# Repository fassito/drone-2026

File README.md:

# Drone-2026

Controladora de vuelo para cuadricóptero basada en **ESP32 (DevKit V1)**,
programada con el **framework Arduino** bajo **PlatformIO**.

## Objetivos del proyecto

1. **Controladora de vuelo en ESP32** con bucle de estabilización a 1 kHz:
   PID en cascada (lazo externo de ángulo + lazo interno de velocidad angular).
2. **Accionamiento de 4 motores brushless** mediante ESC programables
   **BLHeli 30A** con protocolo **OneShot125** (3–6S LiPo).
3. **Doble enlace de comunicación**:
   - **RF** con emisora **FlySky FS-i6** + receptor **FS-IA6B** (protocolo iBus por UART).
   - **WiFi** con interfaz de línea de comandos (CLI) para diagnóstico,
     pruebas y telemetría en tiempo real.
4. **Autoajuste de parámetros PID** para la estabilización.
5. **Seguridad como requisito de primer orden**: armado explícito,
   failsafe de radio y WiFi, corte de motores y procedimientos de prueba seguros.

## Lista de materiales (BOM)

| Componente | Referencia | Notas |
|---|---|---|
| Microcontrolador | ESP32 DevKit V1 (ESP32-WROOM-32, 30 pines) | 240 MHz, dual-core, WiFi |
| Motores | 4× Crozepony DX2205 | 2300 KV, brushless |
| ESC | 4× BLHeli 30A | OneShot125, 3–6S |
| PDB | Power Distribution Board con XT-60 | Reparte la batería a los 4 ESC y al BEC |
| Receptor | FlySky FS-IA6B | 6 canales, iBus UART 115200 |
| Emisora | FlySky FS-i6 | 6 canales, AFHDS 2A, compatible con iBus |
| Batería | LiPo **4S 1550 mAh** (14.8 V) | Alimenta ESCs; BEC/regulador para el ESP32 |
| IMU | MPU-9250 (GY-951) | 9DoF por SPI; fusión Madgwick en el ESP32 a 1 kHz |
| GPS | u-blox NEO-6M-0-001 | NMEA por UART 9600; navegación, waypoints y RTH |
| Monitor de batería | INA219 (I2C) | Monitor de tensión y corriente; alimenta el failsafe de batería baja |
| Barómetro | BMP388 (I2C) | Altitud barométrica para mantener altura con precisión |
| Telemetría en vuelo | HC-12 (433/868/915 MHz) | Enlace bidireccional de comandos/telemetría, fuera de la banda 2.4 GHz |
| Pantalla | OLED I2C ~1" (SSD1306/SH1106) | Telemetría y diagnóstico en pantalla |
| Proximidad | 4× Sharp GP2Y0A21 (IR analógico) | Evitación de choques; salida ADC (ADC1), 10–80 cm |
| Frame + hélices | Cuadricóptero X | Hélice acorde a motor/frame |

## Pendiente de comprar / definir

| Componente | Detalle | Estado |
|---|---|---|
| Frame | Cuadricóptero X ~210–250 mm (fibra de carbono) | 🔴 pendiente |
| Hélices | 5" (p. ej. 5045 tri-blade), 2 CW + 2 CCW + repuestos | 🔴 pendiente |
| BEC 5 V | 5 V / 3 A (los ESC BLHeli 30A son OPTO, sin BEC) | 🔴 pendiente |
| LiPo | **4S 1550 mAh 100C** con XT-60 (DX2205 2300 KV) | 🔴 pendiente |
| Cargador LiPo | Balanceado (IMAX B6 o similar) + bolsa ignífuga | 🔴 pendiente |
| **Nivelador iBus** | Divisor resistivo 5 V→3.3 V (2.2 kΩ + 4.7 kΩ) o módulo nivelador para GPIO34 | 🟡 **obligatorio** |
| Soporte antivibración | Goma/espuma para la IMU MPU-9250 | 🟡 obligatorio |
| Buzzer 5 V | Avisos de armado/failsafe/batería baja (GPIO 15) | 🟡 implementado en código, comprar pieza |
| Monitor de batería | INA219 (ya en BOM) | ✅ decidido |
| Barómetro | BMP388 (ya en BOM) | ✅ decidido |
| Telemetría en vuelo | HC-12 (ya en BOM) | ✅ decidido |

## Arquitectura de subsistemas

```
firmware/
├── src/
│   ├── main.cpp              # Arranque y tareas
│   ├── config.h              # Pines, constantes y parámetros por defecto
│   ├── flight/
│   │   ├── mixer.*           # Mezcla de motores (quad X)
│   │   └── pid.*             # PID en cascada
│   ├── sensors/
│   │   ├── mpu9250.*         # IMU MPU-9250 (SPI) + fusión Madgwick
│   │   └── bmp388.*          # Barómetro BMP388 (altitud barométrica)
│   ├── actuators/
│   │   └── esc.*             # Señal OneShot125
│   ├── radio/
│   │   └── ibus.*            # Decodificación iBus FS-IA6B
│   ├── telemetry/
│   │   ├── wifi_cli.*        # CLI por WiFi (TCP, solo en tierra)
│   │   ├── hc12_link.*       # Radio HC-12 (telemetría/comandos en vuelo)
│   │   └── oled_display.*    # Pantalla OLED I2C (estado y diagnóstico)
│   ├── nav/
│   │   ├── gps.*             # GPS Neo 6M (NMEA), waypoints y RTH
│   │   ├── obstacle.*        # Sensores de proximidad y evitación de choques
│   │   └── mission.*         # Misión autónoma a destino
│   └── safety/
│       ├── failsafe.*        # Armado, failsafe y corte de motores
│       └── power_monitor.*   # Monitor de batería (INA219, I2C)
└── platformio.ini
```

## Personalizaciones incluidas

- **Directrices del proyecto**: [copilot-instructions.md](.github/copilot-instructions.md)
- **Esquema de conexiones (ASCII)**: [docs/conexiones.md](docs/conexiones.md)
- **Agentes especializados**: [.github/agents/](.github/agents/)
- **Skills (flujos de trabajo)**: [.github/skills/](.github/skills/)

## Comandos rápidos

```bash
cd firmware
pio run                        # compilar firmware (ESP32)
pio run -t upload              # grabar firmware
pio device monitor -b 115200   # monitor serie
./run_host_tests.sh            # batería de tests de host (sin hardware)
```

En el dispositivo (con componentes), ejecutar `selftest` desde la CLI (WiFi o HC-12)
para comprobar I2C, IMU, barómetro, batería, receptor, GPS y sensores de proximidad.

## Estado del firmware

El firmware ya está **implementado y compila** (`pio run` → SUCCESS):

| Módulo | Estado |
|---|---|
| `flight/` — PID cascada + mezcla quad X + autoajuste (relé/ZN) | ✅ implementado |
| `nav/` — GPS, obstáculos, misión multi-waypoint, RTH seguro, geofence, altitud, piloto automático | ✅ implementado |
| `sensors/mpu9250.*` — MPU-9250 SPI + Madgwick **9DoF** + calibración mag | ✅ implementado |
| `sensors/bmp388.*` — barómetro I2C | ✅ implementado |
| `safety/` — failsafe (batería/sobrecorriente), INA219, indicadores (buzzer), black box, autotest | ✅ implementado |
| `radio/ibus.*` — FS-IA6B (UART1) | ✅ implementado |
| `actuators/esc.*` — OneShot125 (LEDC) | ✅ implementado |
| `telemetry/` — WiFi CLI, HC-12, OLED, telemetría JSON, OTA | ✅ implementado |
| `main.cpp` — tareas dual-core | ✅ integrado |

**Tests**: batería en host con **136 checks** por componente e integración, más
autotest en dispositivo (`selftest`).

> Pendiente de hardware: calibración de la IMU y del magnetómetro, signos de los
> ejes y ganancias PID definitivas (ver skills `mpu9250-imu` y `pid-autotune`).

## Montaje y test por fases

Los periféricos se activan por flags `ENABLE_*` en [config.h](firmware/src/config.h)
(arrancan en 0 para no leer pines RX flotantes). Enciende cada uno en 1 conforme
lo conectes y valida con `selftest`:

| Fase | Componente | Flag a activar | Verificación |
|---|---|---|---|
| 0 | Solo DevKit | — | monitor serie: `[ctrl] 1000Hz ...` |
| 1 | MPU-9250 (SPI) | `ENABLE_MPU9250` | `selftest` → WHO_AM_I=0x71 |
| 2 | OLED + INA219 + BMP388 | `ENABLE_I2C` | `selftest` + `baro`/`power` |
| 3 | GPS Neo 6M | `ENABLE_GPS` | `gps` → fix=1 al aire libre |
| 4 | HC-12 | `ENABLE_HC12` | `status` por radio desde el PC |
| 5 | FS-IA6B | `ENABLE_IBUS` | `selftest` → enlace activo |
| 6 | Sharp GP2Y0A21 | `ENABLE_SHARP` | `obstacle` → distancias |
| 7 | Potencia + motores | — | `motortest` **sin hélices** |

> ⚠️ **Seguridad**: nunca realizar pruebas con hélices montadas. Toda prueba
> de motores debe hacerse con el armado bloqueado y el failsafe activo.

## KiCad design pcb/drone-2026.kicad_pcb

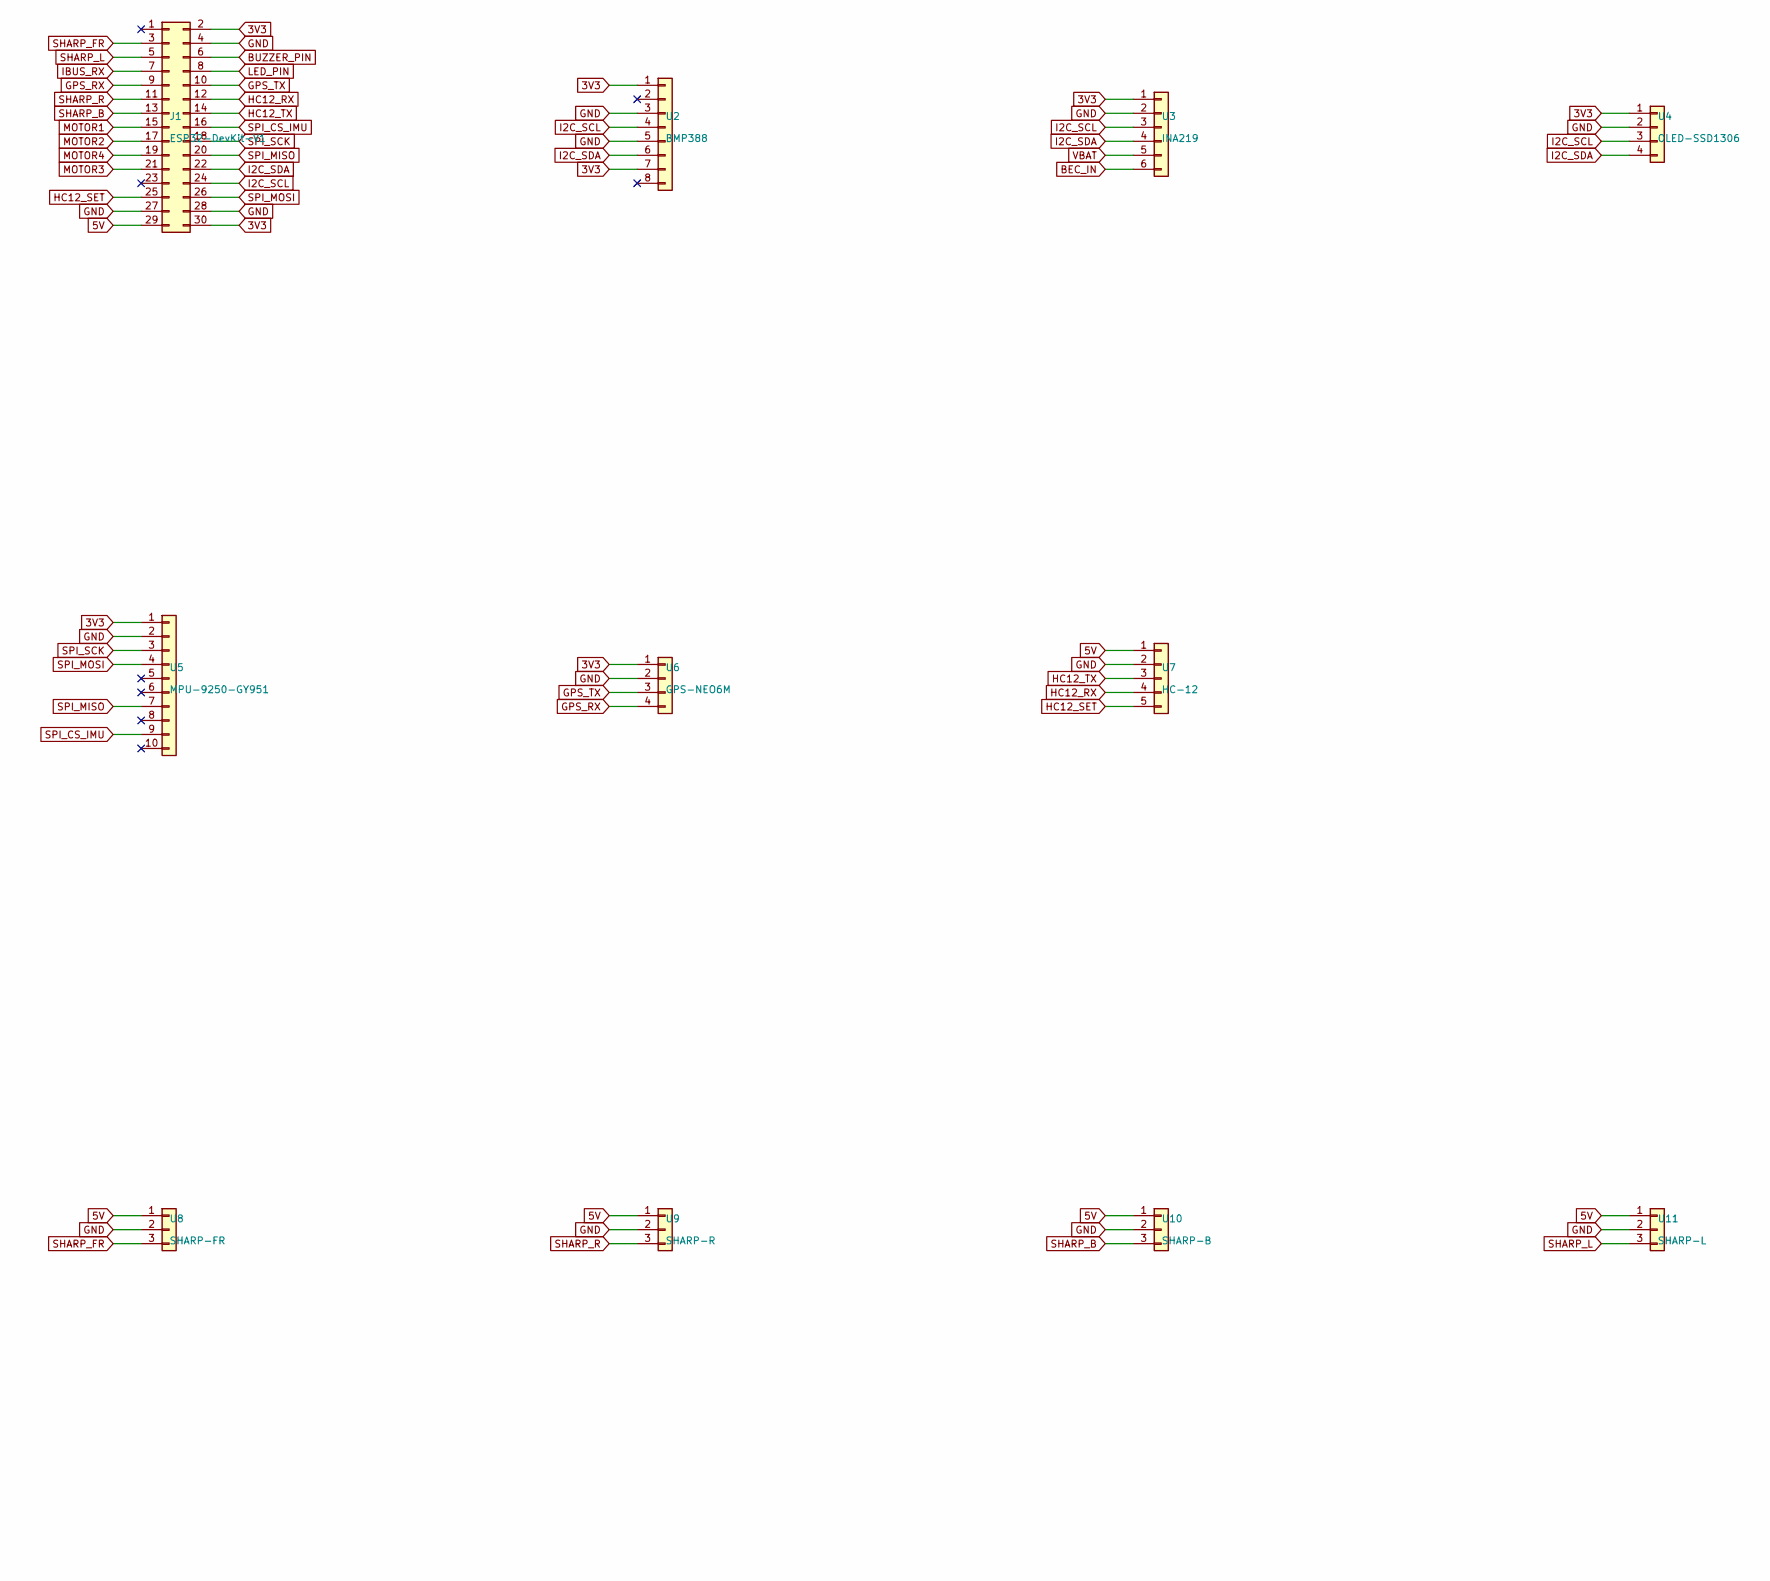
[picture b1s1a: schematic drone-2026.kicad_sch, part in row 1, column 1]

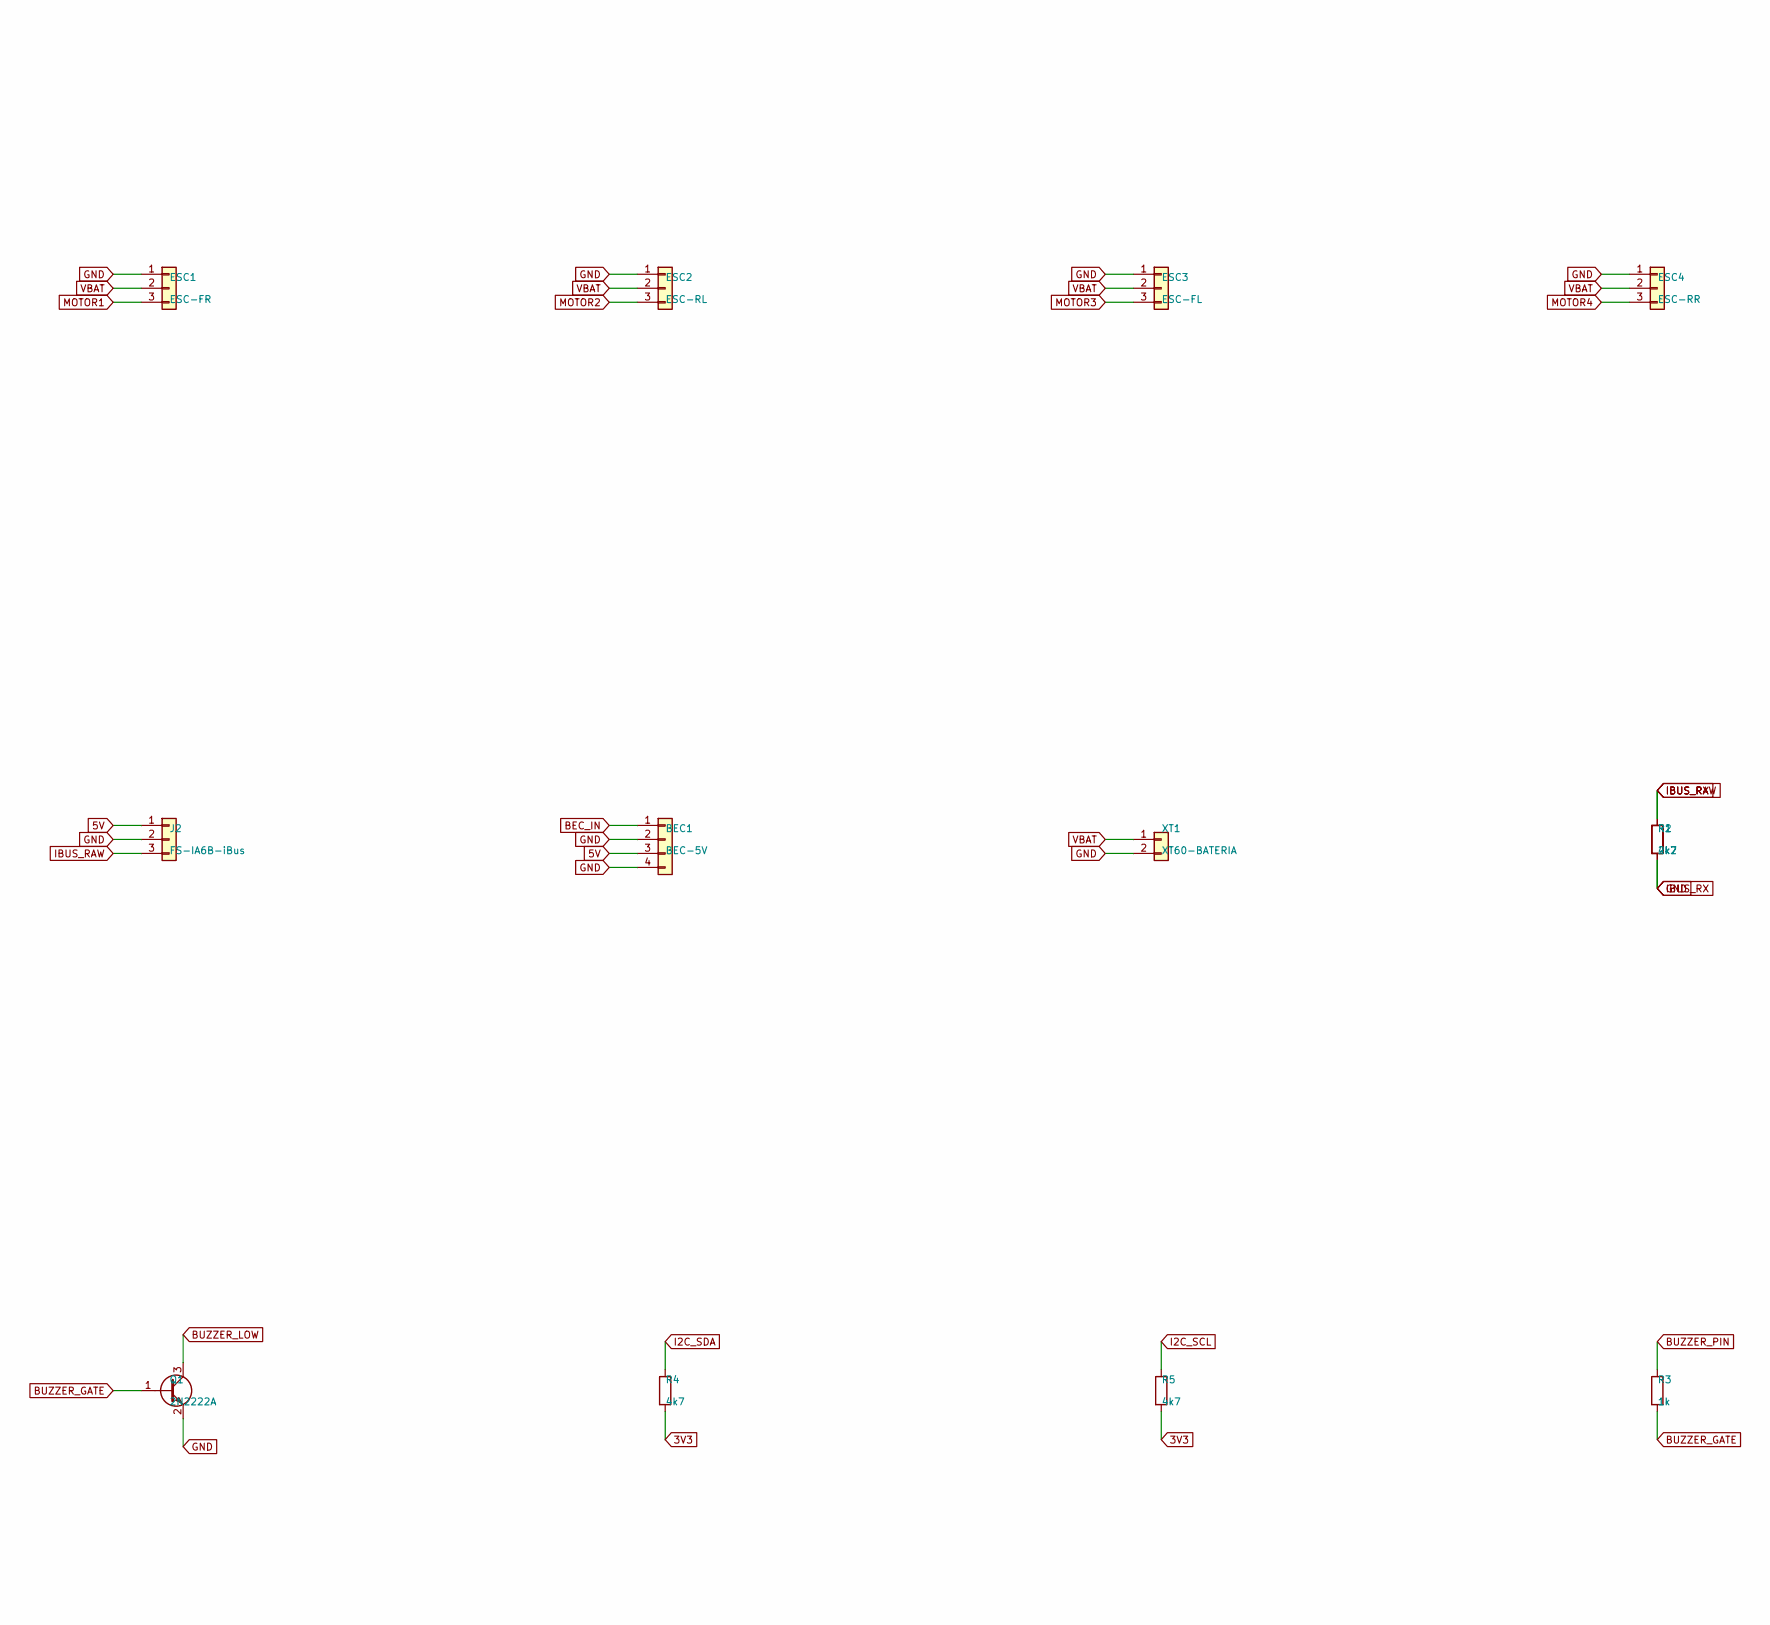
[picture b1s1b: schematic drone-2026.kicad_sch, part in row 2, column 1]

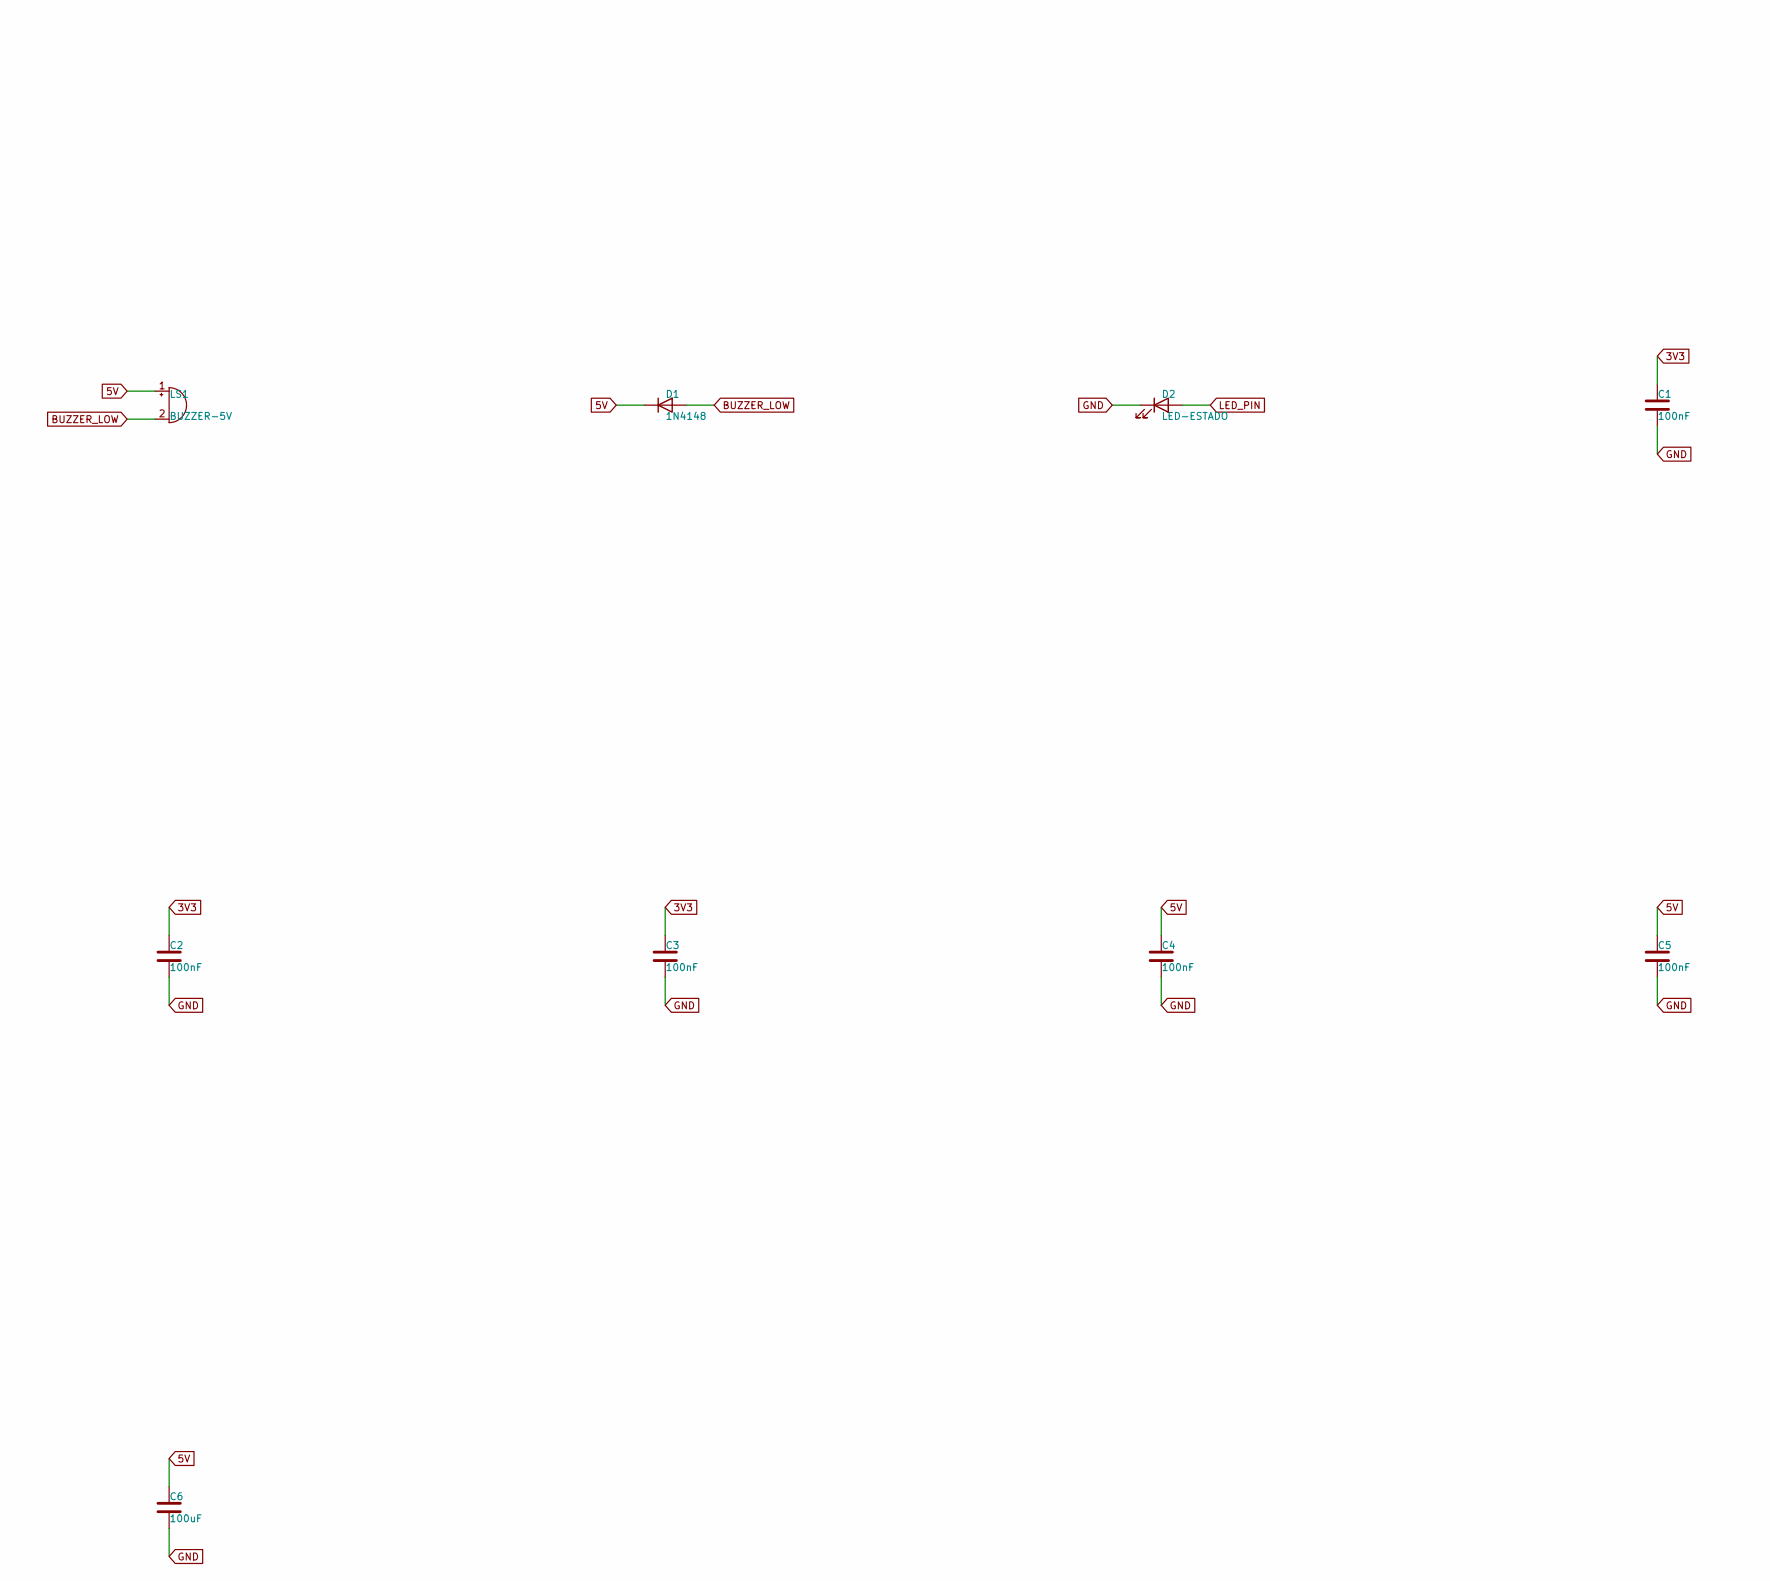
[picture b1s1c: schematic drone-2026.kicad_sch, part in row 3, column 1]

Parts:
BEC1: BEC-5V; PinHeader_1x04_P2.54mm_Vertical
C1, C2, C3, C4, C5: 100nF; C_Disc_D5.0mm_W2.5mm_P2.50mm
C6: 100uF; C_Disc_D5.0mm_W2.5mm_P2.50mm
D1: 1N4148; D_DO-35_SOD27_P7.62mm_Horizontal
D2: LED-ESTADO; LED_D5.0mm
ESC1: ESC-FR; PinHeader_1x03_P2.54mm_Vertical
ESC2: ESC-RL; PinHeader_1x03_P2.54mm_Vertical
ESC3: ESC-FL; PinHeader_1x03_P2.54mm_Vertical
ESC4: ESC-RR; PinHeader_1x03_P2.54mm_Vertical
J1: ESP32-DevKit-V1; PinSocket_2x15_P2.54mm_Vertical
J2: FS-IA6B-iBus; PinHeader_1x03_P2.54mm_Vertical
LS1: BUZZER-5V; Buzzer_12x9.5RM7.6
Q1: 2N2222A; TO-92_Inline
R1: 2k2; R_Axial_DIN0207_L6.3mm_D2.5mm_P7.62mm_Horizontal
R2, R4, R5: 4k7; R_Axial_DIN0207_L6.3mm_D2.5mm_P7.62mm_Horizontal
R3: 1k; R_Axial_DIN0207_L6.3mm_D2.5mm_P7.62mm_Horizontal
U2: BMP388; PinHeader_1x08_P2.54mm_Vertical
U3: INA219; PinHeader_1x06_P2.54mm_Vertical
U4: OLED-SSD1306; PinHeader_1x04_P2.54mm_Vertical
U5: MPU-9250-GY951; PinHeader_1x10_P2.54mm_Vertical
U6: GPS-NEO6M; PinHeader_1x04_P2.54mm_Vertical
U7: HC-12; PinHeader_1x05_P2.54mm_Vertical
U8: SHARP-FR; PinHeader_1x03_P2.54mm_Vertical
U9: SHARP-R; PinHeader_1x03_P2.54mm_Vertical
U10: SHARP-B; PinHeader_1x03_P2.54mm_Vertical
U11: SHARP-L; PinHeader_1x03_P2.54mm_Vertical
XT1: XT60-BATERIA; PinHeader_1x02_P2.54mm_Vertical

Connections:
3V3: C1.1, C2.1, C3.1, J1.2, J1.30, R4.2, R5.2, U2.1, U2.7, U3.1, U4.1, U5.1, U6.1
5V: BEC1.3, C4.1, C5.1, C6.1, D1.1 (K), J1.29, J2.1, LS1.1 (+), U7.1, U8.1, U9.1, U10.1, U11.1
BEC_IN: BEC1.1, U3.6
BUZZER_GATE: Q1.1 (B), R3.2
BUZZER_LOW: D1.2 (A), LS1.2 (-), Q1.3 (C)
BUZZER_PIN: J1.6, R3.1
GPS_RX: J1.9, U6.4
GPS_TX: J1.10, U6.3
HC12_RX: J1.12, U7.4
HC12_SET: J1.25, U7.5
HC12_TX: J1.14, U7.3
I2C_SCL: J1.24, R5.1, U2.4, U3.3, U4.3
I2C_SDA: J1.22, R4.1, U2.6, U3.4, U4.4
LED_PIN: D2.2 (A), J1.8
MOTOR1: ESC1.3, J1.15
MOTOR2: ESC2.3, J1.17
MOTOR3: ESC3.3, J1.21
MOTOR4: ESC4.3, J1.19
SHARP_B: J1.13, U10.3
SHARP_FR: J1.3, U8.3
SHARP_L: J1.5, U11.3
SHARP_R: J1.11, U9.3
SPI_CS_IMU: J1.16, U5.9
SPI_MISO: J1.20, U5.7
SPI_MOSI: J1.26, U5.4
SPI_SCK: J1.18, U5.3
VBAT: ESC1.2, ESC2.2, ESC3.2, ESC4.2, U3.5, XT1.1

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
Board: 2 copper layers, 37 parts (0 on the bottom side), 30 nets, no tracks yet.

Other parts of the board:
H1, H2, H3, H4: MountingHole_3.2mm_M3

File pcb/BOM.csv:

Referencia,Componente,Pines,Nota
BEC1,BEC 5V,4,
D1,Flyback 1N4148,2,
D2,LED estado,2,
ESC1,ESC 1,3,
ESC2,ESC 2,3,
ESC3,ESC 3,3,
ESC4,ESC 4,3,
J1,ESP32 DevKit V1,25,
J2,FS-IA6B iBus,3,
LS1,Buzzer 5V,2,
Q1,NPN 2N2222,3,
R1,Divisor 2.2k,2,
R2,Divisor 4.7k,2,
R3,Base 1k,2,
U10,Sharp B,3,
U11,Sharp L,3,
U2,BMP388 CJMCU-388,6,
U3,INA219,6,
U4,OLED SSD1306,4,
U5,MPU-9250 GY-951,6,
U6,GPS Neo 6M,4,
U7,HC-12,5,
U8,Sharp FR,3,
U9,Sharp R,3,
XT1,XT-60 batería,2,

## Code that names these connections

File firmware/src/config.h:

#pragma once

// ============================================================
// Drone-2026 — Configuración de hardware y constantes
// Placa: ESP32 DevKit V1 (ESP32-WROOM-32, 30 pines)
// ============================================================

#define BOARD_NAME "ESP32 DevKit V1"

// ---------- Puertos serie ----------
#define MONITOR_SPEED 115200

// ---------- Pines ----------
// Motores (OneShot125) — salidas LEDC de alta resolución.
// Se evitan los pines de strapping (GPIO12/MTDI y GPIO15/MTDO) para no
// condicionar el arranque: un nivel erróneo en ellos impide bootear.
#define MOTOR_PIN_1 25
#define MOTOR_PIN_2 26
#define MOTOR_PIN_3 14
#define MOTOR_PIN_4 27

// Receptor FS-IA6B (iBus, UART). GPIO34 es solo de entrada.
#define IBUS_UART_NUM 1
#define IBUS_RX_PIN 34
#define IBUS_TX_PIN (-1)   // no se usa TX

// IMU MPU-9250 (GY-951, SPI). Giroscopio/acelerómetro/magnetómetro + fusión
// Madgwick en el ESP32 a 1 kHz.
#define MPU9250_SPI_SCK  18
#define MPU9250_SPI_MOSI 23
#define MPU9250_SPI_MISO 19
#define MPU9250_SPI_CS   5
#define MPU9250_SPI_HZ   10000000   // 10 MHz
#define MPU9250_USE_MAG  1          // usar magnetómetro AK8963 (9DoF)

// GPS Neo 6M-0-001 (NMEA). El GPS (9600 baud) va por SoftwareSerial.
#define GPS_BAUD 9600
#define GPS_RX_PIN 35     // solo entrada
#define GPS_TX_PIN 4      // requerido por la librería aunque no se use TX

// Radio de telemetría HC-12 (433/868/915 MHz). En UART2 de hardware (pines
// 16/17 libres). 9600 baud. Enlace EN VUELO.
#define HC12_BAUD 9600
#define HC12_UART_NUM 2
#define HC12_RX_PIN 16    // HC-12 TX -> ESP32 RX2
#define HC12_TX_PIN 17    // HC-12 RX <- ESP32 TX2
#define HC12_SET_PIN 13   // HIGH = modo AT, LOW = transparente

// Bus I2C (pantalla OLED y sensores I2C futuros)
#define I2C_SDA_PIN 21
#define I2C_SCL_PIN 22

// Pantalla OLED I2C (~1 pulgada, SSD1306/SH1106) — comparte el bus I2C.
#define OLED_I2C_ADDR 0x3C
#define OLED_WIDTH 128
#define OLED_HEIGHT 64

// Monitor de batería INA219 (I2C) — comparte el bus I2C con la OLED.
#define INA219_I2C_ADDR 0x40
// LiPo 4S (14.8 V nominal). Aviso a 3.50 V/celda y corte a 3.30 V/celda:
// por debajo de 3.3 V la celda se degrada de forma irreversible.
#define BATTERY_LOW_V     14.0f   // 4S: 3.50 V/celda → aterrizar
#define BATTERY_CELLS    4        // celdas de la LiPo (4S)
#define BATTERY_CAPACITY_MAH 1550 // capacidad nominal del pack, para estimar mAh

// Barómetro BMP388 (I2C) — comparte el bus I2C con OLED e INA219.
#define BMP388_I2C_ADDR 0x76     // 0x77 si el pin SDO del BMP388 está a VCC
#define BMP388_SDO_HIGH false    // true si SDO está a VCC (cambia la dirección a 0x77)

// Sensores de proximidad (evitar choques): 4x Sharp GP2Y0A21 (IR analógico,
// 10–80 cm) en los canales ADC1. Solo se usan los ADC1 expuestos en el
// DevKit V1 de 30 pines (36, 39, 32, 33): GPIO37/38 no salen al conector.
// ADC2 entra en conflicto con el WiFi activo, por eso no se usan.
#define PROX_SENSOR_COUNT 4
#define PROX_PIN_FRONT  36   // VP
#define PROX_PIN_RIGHT  32
#define PROX_PIN_BACK   33
#define PROX_PIN_LEFT   39   // VN

// LED de estado integrado
#define LED_BUILTIN 2

// Buzzer 5V (avisos de armado/failsafe/batería baja).
// GPIO15 es pin de strapping (MTDO): queda alto al arrancar y la base del
// transistor (1k) no lo fuerza, así que no afecta al boot.
#define BUZZER_PIN 15

// ---------- Seguridad (failsafe) ----------
#define BATTERY_CRITICAL_V 13.2f   // 4S: 3.30 V/celda → corte de motores
// Por debajo de esto la lectura no es creíble (INA219 sin Vin+/Vin-
// cableados, o sensor desconectado): el failsafe de tensión se inhibe para
// no confundir "sensor ausente" con "batería agotada".
#define BATTERY_MIN_PLAUSIBLE_V 6.0f
// El INA219 mide solo la rama del BEC (la corriente de los motores no pasa
// por su shunt de 0.1 Ω). Este límite detecta un cortocircuito en la
// electrónica, no una hélice bloqueada: eso lo cubren la caída de tensión y
// el límite de inclinación.
#define MAX_CURRENT_A       2.0f

// ---------- Habilitación de periféricos ----------
// Encender cada uno en 1 conforme se conecte (evita leer pines RX flotantes).
// Fase 0 (solo DevKit): todo en 0 salvo WiFi.
#define ENABLE_MPU9250  1    // IMU SPI (Fase 1)
#define ENABLE_I2C      1    // OLED + INA219 + BMP388 (Fase 2)
#define ENABLE_GPS      0    // Neo 6M (Fase 3)
#define ENABLE_HC12     0    // radio telemetría (Fase 4)
#define ENABLE_IBUS     0    // FS-IA6B (Fase 5)
#define ENABLE_SHARP    0    // GP2Y0A21 ADC (Fase 6)
#define ENABLE_INA219   1    // monitor de batería (Fase 2)

// ---------- Bucle de control ----------
#define LOOP_FREQ_HZ 1000
#define LOOP_PERIOD_US (1000000 / LOOP_FREQ_HZ)
// Núcleo dedicado AL control de vuelo (core 0). Las comunicaciones, sensores
// auxiliares y UI van en el core 1 (donde Arduino ejecuta setup()/loop()).
#define CONTROL_TASK_CORE 0
#define CONTROL_TASK_PRIORITY 10

// ---------- OneShot125 (ESC BLHeli 30A) ----------
#define ONESHOT_MIN_US 125
#define ONESHOT_MAX_US 250
#define ONESHOT_NEUTRAL_US 188
#define ONESHOT_REFRESH_HZ 500   // periodo fijo de 2 ms

// ---------- iBus (FS-IA6B) ----------
#define IBUS_BAUD 115200
#define IBUS_CHANNELS 6

// ---------- Navegación autónoma ----------
#define RTH_ALT_M            5.0f    // altitud de seguridad para RTH
#define GEOFENCE_MAX_DIST_M  200.0f  // radio máximo desde home
#define GEOFENCE_MAX_ALT_M   50.0f   // altitud máxima

// ---------- Black box (registro en vuelo, RAM) ----------
#define BLACKBOX_RATE_HZ      100
#define BLACKBOX_MAX_SAMPLES  1000    // ~10 s a 100 Hz

// ---------- WiFi CLI (solo tierra) ----------
#define WIFI_AP_SSID "Drone-2026"
#define WIFI_AP_PASS "cambia-esta-clave"
#define CLI_TCP_PORT 23
#define OTA_HOSTNAME "drone-2026"

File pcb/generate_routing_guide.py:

#!/usr/bin/env python3
"""Genera GUIA_ENRUTADO.md con las conexiones pendientes y sus coordenadas.

  flatpak run --command=python3 org.kicad.KiCad pcb/generate_routing_guide.py
"""
import os
from collections import defaultdict
import pcbnew

HERE = os.path.dirname(os.path.abspath(__file__))
PCB = os.path.join(HERE, "drone-2026.kicad_pcb")
OUT = os.path.join(HERE, "GUIA_ENRUTADO.md")

# orden de enrutado y anchura recomendada (mm)
ORDER = [
    ("VBAT", 1.5, "Potencia: batería → ESC. Lo más corto y ancho posible."),
    ("5V", 0.8, "Alimentación de la electrónica desde el BEC."),
    ("3V3", 0.8, "Alimentación de sensores desde el regulador del DevKit."),
    ("I2C_SDA", 0.3, "Rutear junto a I2C_SCL, en paralelo."),
    ("I2C_SCL", 0.3, "Rutear junto a I2C_SDA, en paralelo."),
    ("SPI_SCK", 0.3, "Bus SPI de la IMU: mantener corto."),
    ("SPI_MOSI", 0.3, "Bus SPI de la IMU."),
    ("SPI_MISO", 0.3, "Bus SPI de la IMU."),
    ("SPI_CS_IMU", 0.3, "Bus SPI de la IMU."),
    ("IBUS_RAW", 0.3, "Señal del receptor al divisor."),
    ("IBUS_RX", 0.3, "Salida del divisor al GPIO34."),
    ("MOTOR1", 0.3, "Señal OneShot125 al ESC."),
    ("MOTOR2", 0.3, "Señal OneShot125 al ESC."),
    ("MOTOR3", 0.3, "Señal OneShot125 al ESC."),
    ("MOTOR4", 0.3, "Señal OneShot125 al ESC."),
    ("GPS_TX", 0.3, "UART del GPS."),
    ("GPS_RX", 0.3, "UART del GPS."),
    ("HC12_TX", 0.3, "UART2 del HC-12."),
    ("HC12_RX", 0.3, "UART2 del HC-12."),
    ("HC12_SET", 0.3, "Modo AT del HC-12."),
    ("SHARP_FR", 0.3, "Analógica del sensor frontal."),
    ("SHARP_R", 0.3, "Analógica del sensor derecho."),
    ("SHARP_B", 0.3, "Analógica del sensor trasero."),
    ("SHARP_L", 0.3, "Analógica del sensor izquierdo."),
    ("LED_PIN", 0.3, "LED de estado."),
    ("BUZZER_PIN", 0.3, "GPIO del buzzer a la base del transistor."),
    ("BUZZER_GATE", 0.3, "Base del transistor a la resistencia."),
    ("BUZZER_LOW", 0.3, "Colector del transistor al buzzer y al diodo."),
    ("BEC_IN", 1.0, "Entrada del BEC, a través del shunt del INA219."),
]


def nearest_order(pts):
    """Encadena los pads por cercanía para que la ruta fluya."""
    rest = list(pts)
    out = [rest.pop(0)]
    while rest:
        last = out[-1]
        k = min(range(len(rest)),
                key=lambda i: (rest[i][2] - last[2]) ** 2 + (rest[i][3] - last[3]) ** 2)
        out.append(rest.pop(k))
    return out


def main():
    board = pcbnew.LoadBoard(PCB)
    pads = defaultdict(list)
    for fp in board.GetFootprints():
        for p in fp.Pads():
            n = p.GetNetname()
            if not n or n == "GND":
                continue
            pos = p.GetPosition()
            pads[n].append((fp.GetReference(), p.GetNumber(),
                            pcbnew.ToMM(pos.x), pcbnew.ToMM(pos.y)))

    xs, ys = [], []
    for d in board.GetDrawings():
        if d.GetLayer() == pcbnew.Edge_Cuts:
            bb = d.GetBoundingBox()
            xs += [pcbnew.ToMM(bb.GetLeft()), pcbnew.ToMM(bb.GetRight())]
            ys += [pcbnew.ToMM(bb.GetTop()), pcbnew.ToMM(bb.GetBottom())]

    lines = []
    lines.append("# Guía de enrutado — placa Drone-2026\n")
    lines.append("Placa de **%.0f × %.0f mm**, 2 capas (`F.Cu` / `B.Cu`). "
                 "Los componentes ya están colocados y las redes asignadas: solo "
                 "faltan las pistas.\n" % (max(xs) - min(xs), max(ys) - min(ys)))
    lines.append("Coordenadas en mm con el origen en la esquina superior "
                 "izquierda (Y crece hacia abajo, como en KiCad).\n")
    lines.append("\n## Antes de empezar\n")
    lines.append("1. **GND no aparece aquí**: se resuelve con un plano de masa. "
                 "En el editor de PCB: `Añadir zona rellena` → capa `B.Cu` → "
                 "red `GND` → dibuja el rectángulo del contorno → `B` para "
                 "rellenar. (También puedes usar `pcb/add_gnd_zone.py`.)")
    lines.append("2. Traza en el orden de esta guía: primero potencia (ancha), "
                 "luego buses y por último señales.")
    lines.append("3. Atajo en KiCad: pulsa `X` para enrutar, `V` para poner una "
                 "vía, `B` para rellenar zonas.")
    lines.append("\n## Redes a conectar\n")

    idx = 0
    for name, width, note in ORDER:
        pts = pads.get(name, [])
        if len(pts) < 2:
            continue
        pts = nearest_order(pts)
        idx += 1
        total = sum(((x2 - x1) ** 2 + (y2 - y1) ** 2) ** 0.5
                    for (_, _, x1, y1), (_, _, x2, y2) in zip(pts, pts[1:]))
        lines.append("### %d. `%s` — pista de %.1f mm  (%.0f mm en total)\n"
                     % (idx, name, width, total))
        lines.append("*%s*\n" % note)
        path = "  →  ".join("%s.%s (%.1f, %.1f)"
                           % (r, pn, x, y) for r, pn, x, y in pts)
        lines.append("%s\n" % path)

    lines.append("\n## Consejos por bloque\n")
    lines.append("- **VBAT**: de XT1 a los 4 ESC y a INA219. Es la de más "
                 "corriente: usa 1.5 mm o más y evita rodeos.")
    lines.append("- **BEC_IN**: pasa por el shunt del INA219 (Vin+ / Vin−). "
                 "Respétalo o la medición de corriente no funciona.")
    lines.append("- **I2C_SDA / SCL**: trázalas en paralelo y cortas; compartidas "
                 "por OLED, BMP388 e INA219.")
    lines.append("- **SPI**: SCK/MOSI/MISO/CS de la IMU al DevKit. Mantenlas "
                 "juntas y lejos de VBAT para evitar ruido.")
    lines.append("- **MOTOR1-4**: solo señal, 0.3 mm. Van del DevKit a cada ESC.")
    lines.append("- **Divisor iBus**: R1 (2k2) en serie desde IBUS_RAW y R2 "
                 "(4k7) a GND en el lado IBUS_RX.")
    lines.append("- **Buzzer**: BUZZER_PIN → R3 (1k) → BUZZER_GATE (base de Q1); "
                 "Q1 colector → BUZZER_LOW; diodo D1 en paralelo con el buzzer.\n")
    lines.append("\n## Al terminar\n")
    lines.append("1. Rellena el plano de GND (`B`).")
    lines.append("2. `Inspeccionar → Reglas de diseño` debe dar **0 violaciones** "
                 "y **0 elementos sin conectar**.")
    lines.append("3. `Archivo → Fabricación → Gerbers` para mandar a fabricar.\n")

    open(OUT, "w", encoding="utf-8").write("\n".join(lines) + "\n")
    print("guía escrita -> %s (%d redes)" % (OUT, idx))


if __name__ == "__main__":
    main()
